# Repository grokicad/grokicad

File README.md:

# GroKi

 AI-powered KiCad understanding for humans. GroKi distills complex schematics into structured data, streams AI explanations, and tracks changes across hardware repos so other engineers, reviewers, and stakeholders (not just EEs) can see what changed, why, and where to look next. Try it out at https://grokicad.com.

## Why
Most people looking at schematics aren’t the original EE, and they need clarity more than another AI authoring tool. Netlists are hard to read, version-control diffing is clunky, and AI tools rarely speak KiCad. GroKi bridges that gap for reviewers, systems engineers, firmware teams, and judges: it parses KiCad projects, summarizes commits and selections with Grok, searches parts, and serves an interactive viewer workflow.

## Key Features
- **Schematic distillation**: Python distiller (`schematic-distiller/`, powered by `kicad-sch-api`) converts `.kicad_sch` into normalized JSON (components, nets, proximities) with cacheable results.
- **Repo + commit intelligence**: Rust backend (`backend/`, Axum + utoipa) initializes repos, lists schematic commits/files, and surfaces commit metadata plus cached distillations.
- **AI assistance (Grok)**:
  - Commit, selection, and repo summaries (`/api/grok/*`)
  - Streaming SSE analysis for selected components with semantic context
  - Obsolete-part replacement suggestions
- **Distill-on-demand API**: `/api/distill` runs or returns cached distillations; `/api/repo/init` primes a repo and reports component/net counts.
- **Part search**: DigiKey keyword/MPN lookup with graceful fallback when not configured.
- **Viewer-friendly data**: Works with `kicanvas/` (TypeScript/WebGL KiCad viewer) and includes ready-made KiCad samples for demos.
- **Example repos**: Use the provided KiCad projects for instant demos:
  - uBMS-2 battery management system: https://github.com/CwbhX/uBMS-2
  - Grok KiCad Watch: https://github.com/CwbhX/GrokKiCADWatch

## Architecture (high level)
- **schematic-distiller/**: Python package + docs; uses `kicad-sch-api` for lossless parsing, connectivity, hierarchy, BOM properties, and MCP tooling.
- **backend/**: Rust Axum service exposing REST + Swagger UI, SSE endpoints, Grok integrations, DigiKey client, and git helpers.
- **database/**: PostgreSQL (Docker) plus Rust `kicad-db` crate for storing distilled JSON, schematic blurbs/overviews, and part metadata.
- **kicanvas/**: Browser-based KiCad viewer (TypeScript/WebGL). Ships with a static debug viewer and docs for embedding.
- **kicad-example-files/**: Curated KiCad projects (includes uBMS-2 and SmartWatch) for quick demonstrations.
- **grokprompts/**: System prompt used by Grok selection summaries.

## Quickstart (judge-friendly)
Prereqs: Docker (for Postgres), Rust toolchain, Python 3.10+, Node (only if you want to rebuild KiCanvas), env var `XAI_API_KEY` for Grok, optional `DIGIKEY_CLIENT_ID/SECRET`.

1) Start the database  
```bash
cd database
chmod +x *.sh
./database-up.sh
```

2) Run the backend (Swagger served at `/swagger-ui`)  
```bash
cd backend
cargo run
# Server on :8080 by default
```

3) Initialize a repo and distill schematics (example: uBMS-2)  
```bash
curl -X POST http://localhost:8080/api/repo/init \
  -H "Content-Type: application/json" \
  -d '{"repo":"CwbhX/uBMS-2"}'
# Response includes component/net counts, schematic file list, and distilled JSON (cached afterward)
```

4) Get commit file list or info  
```bash
curl -X POST http://localhost:8080/api/repo/commit/files \
  -H "Content-Type: application/json" \
  -d '{"repo":"CwbhX/uBMS-2","commit":"<hash>"}'
```

5) Ask Grok for a selection summary (streaming SSE)  
```bash
curl -N -X POST http://localhost:8080/api/grok/selection/stream \
  -H "Content-Type: application/json" \
  -d '{
        "repo":"CwbhX/uBMS-2",
        "commit":"<hash>",
        "component_ids":["U1","R3","C5"],
        "query":"Explain what these parts do together.",
        "thinking_mode":false
      }'
```

6) Try DigiKey search (optional)  
```bash
curl -X POST http://localhost:8080/api/digikey/search \
  -H "Content-Type: application/json" \
  -d '{"query":"ESP32-WROOM"}'
```

7) View data in Swagger UI  
Open `http://localhost:8080/swagger-ui/` to exercise all endpoints.

## Demo scripts & viewer notes
- Use `kicad-example-files/BMS` for uBMS-2 and `kicad-example-files/Smart Watch` for the watch project—both mirror the example repos above.
- `kicanvas/debug/index.html` (or `schematic.html`) can be used to point at distilled outputs or KiCad files if you want an in-browser viewer during judging.

## Developer guide (quick map)
- `backend/src/controllers/…`: Route handlers for repo, distill, grok (AI summaries + SSE), hook (webhooks/refresh), digikey.  
- `backend/src/services/…`: Git helpers, distill runner, DigiKey client.  
- `backend/src/openapi.rs`: Swagger/OpenAPI registration.  
- `database/src`: `kicad-db` crate and scripts to manage Postgres.  
- `schematic-distiller/docs`: Deep docs: getting started, API reference, hierarchy, MCP setup, known limitations.  
- `kicanvas/src`: TypeScript viewer core; `docs/` covers embedding and dev setup.  
- `grokprompts/`: System prompt text used by Grok selection streaming.

## Tips for demos
- **Cache wins**: `/api/repo/init` and `/api/distill` cache distilled JSON in Postgres; repeat calls are instant.  
- **Selections**: Provide explicit `component_ids` to `/api/grok/selection/stream` for tighter answers.  
- **Fallbacks**: If DigiKey creds are missing, the API responds with a clear “not configured” message.  
- **Rate limits**: Grok endpoints call external APIs; if rate-limited, re-run after a short pause.

## Requirements & assumptions
- KiCad 6/7/8 schematics are supported (KiCanvas is v6+; custom fonts in v7 may have gaps).  
- Postgres must be running for caching and part storage.  
- `XAI_API_KEY` required for Grok endpoints; without it, only non-AI paths (distill, repo metadata) will function.  
- Docker scripts reset data when recreating the DB container.

## Known limitations
- Advanced ERC and full global-label connectivity are partial in the underlying parser (see `schematic-distiller/docs/KNOWN_LIMITATIONS.md`).  
- Some Grok endpoints still return placeholder text when external services are unavailable.  
- Viewer: KiCad 5 files are unsupported; best on Chrome/Firefox/Safari desktop.

## Acknowledgments
- Built on `kicad-sch-api`, KiCanvas, Axum, sqlx, and Grok APIs.  
- Example hardware from uBMS-2 and Grok KiCad Watch repos cited above.  
- Created for hackathon judging—fast setup, clear outputs, and transparent architecture.

## Creators
- Clement Hathaway
- Ernest Yeung
- Evan Hekman
- Julian Carrier

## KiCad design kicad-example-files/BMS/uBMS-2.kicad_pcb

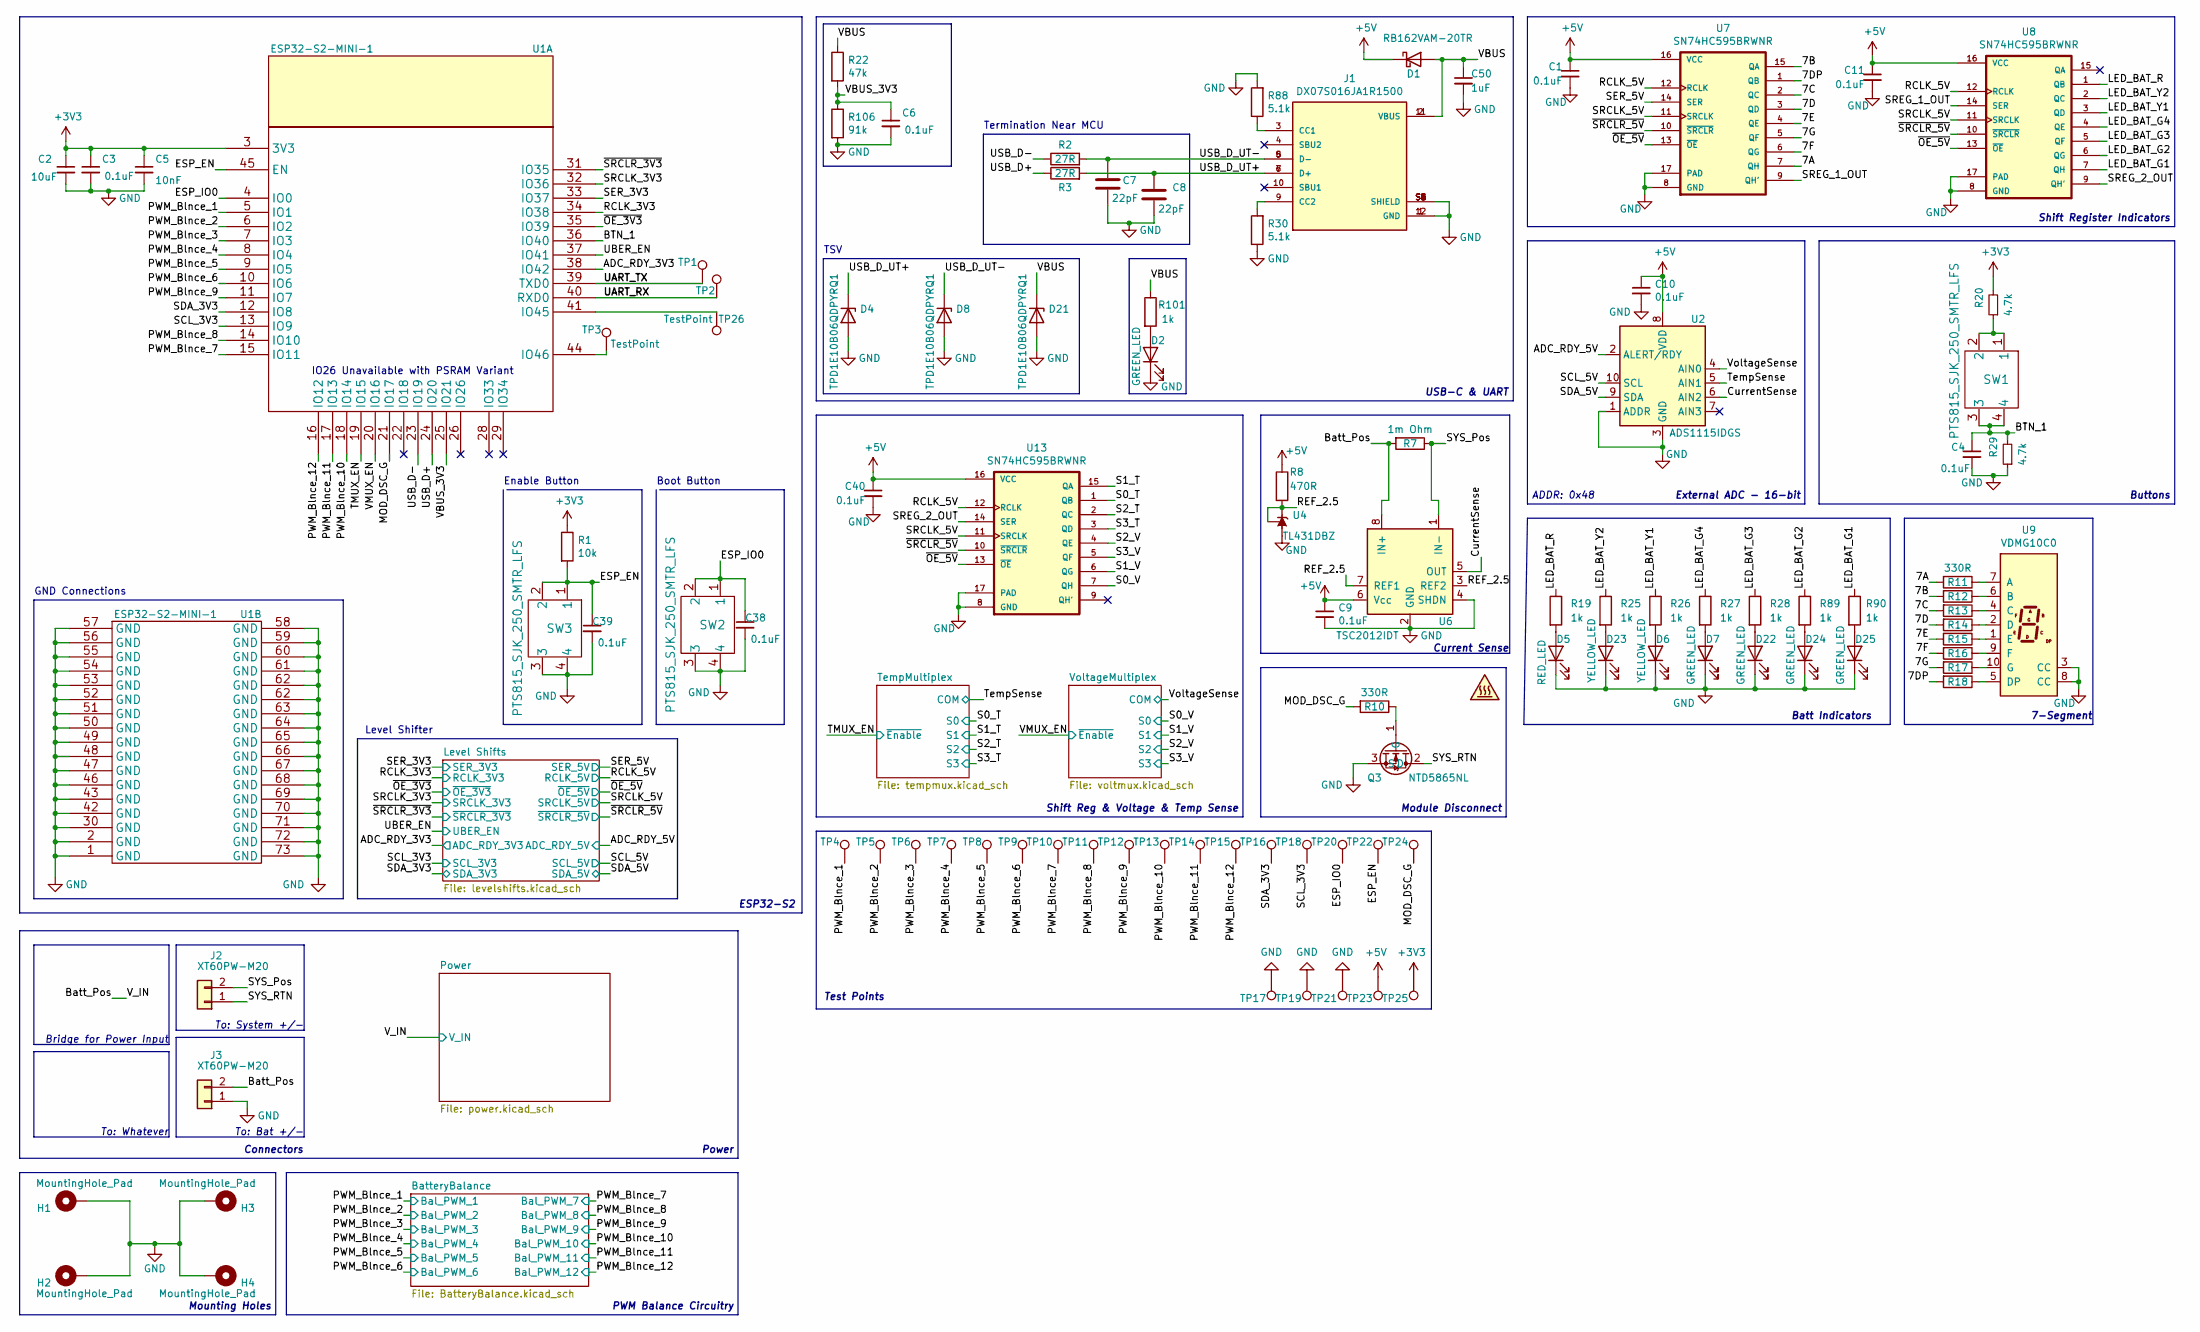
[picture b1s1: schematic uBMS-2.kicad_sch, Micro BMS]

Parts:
C1, C3, C4, C6, C9, C10, C11, C38, C39, C40: 0.1uF; C_0402_1005Metric; Part Number CC0402KRX7R7BB104; Digikey Number 311-1338-1-ND
C2: 10uF; C_0805_2012Metric; Part Number C0805C106K8PACTU; Digikey Number 399-4925-2-ND
C5: 10nF; C_0402_1005Metric; Part Number GCM155R71H103KA55D; Digikey Number 490-4762-1-ND
C7, C8: 22pF; C_0402_1005Metric; Part Number GRM1555C1H220JA01D; Digikey Number 490-5868-1-ND
C50: 1uF; C_0805_2012Metric; Part Number C0805C105Z4VACTU; Digikey Number 399-8011-2-ND
D1: RB162VAM-20TR; D_TUMD2; Part Number RB162VAM-20TR; Digikey Number RB162VAM-20TRTR-ND
D2, D7, D22, D24, D25: GREEN_LED; LED_0603_1608Metric; Part Number 150060VS55040; Digikey Number 732-12017-2-ND
D4, D8, D21: TPD1E10B06QDPYRQ1; D_0402_1005Metric; Part Number TPD1E10B06QDPYRQ1; Digikey Number 296-TPD1E10B06QDPYRQ1TR-ND
D5: RED_LED; LED_0603_1608Metric; Part Number 150060SS55040; Digikey Number 732-12016-2-ND
D6, D23: YELLOW_LED; LED_0603_1608Metric; Part Number 150060YS55040; Digikey Number 732-12018-2-ND
H1, H2, H3, H4: MountingHole_Pad; MountingHole_2.5mm_Pad_TopBottom
J1: DX07S016JA1R1500; PARTREV 1; Digikey Number 670-DX07S016JA1R1500TR-ND
J2, J3: XT60PW-M20
Q3: NTD5865NL; TO-252-2; Part Number NTD5865NLT4G; Digikey Number NTD5865NLT4GOSTR-ND
R1: 10k; R_0402_1005Metric; Part Number RC0402FR-0710KL; Digikey Number 311-10.0KLRCT-ND
R2, R3: 27R; R_0402_1005Metric; Part Number RC0402FR-0727RL; Digikey Number YAG3086CT-ND
R7: 1m Ohm; R_2512_CSNL2512; Part Number CSNL2512FT1L00; Digikey Number CSNL2512FT1L00TR-ND
R8: 470R; R_0402_1005Metric; Part Number RC0402FR-07470RL; Digikey Number 311-470LRCT-ND
R10, R11, R12, R13, R14, R15, R16, R17, R18: 330R; R_0402_1005Metric; Part Number RC0402FR-07330RL; Digikey Number 311-330LRCT-ND
R19, R25, R26, R27, R28, R89, R90, R101: 1k; R_0402_1005Metric; Part Number RC0402FR-071KL; Digikey Number 311-1.00KLRCT-ND
R20, R29: 4.7k; R_0402_1005Metric; Part Number RC0402FR-074K7L; Digikey Number 311-4.7KLRCT-ND
R22: 47k; R_0402_1005Metric; Part Number RC0402FR-0747KL; Digikey Number 311-47.0KLRCT-ND
R30, R88: 5.1k; R_0402_1005Metric; Part Number RC0402FR-075K1L; Digikey Number 311-5.10KLRCT-ND
R106: 91k; R_0402_1005Metric; Part Number RC0402FR-0791KL; Digikey Number 311-91.0KLRCT-ND
SW1, SW2, SW3: PTS815_SJK_250_SMTR_LFS; Part Number PTS815_SJK_250_SMTR_LFS; Digikey Number CKN12216-2-ND
TP1, TP2, TP3, TP4, TP5, TP6, TP7, TP8, TP9, TP10, TP11, TP12, TP13, TP14, TP15, TP16, TP17, TP18, TP19, TP20, TP21, TP22, TP23, TP24, TP25, TP26: TestPoint; TestPoint_Pad_D1.0mm
U1: ESP32-S2-MINI-1
U2: ADS1115IDGS; TSSOP-10_3x3mm_P0.5mm; Part Number ADS1115IDGSR; Digikey Number 296-38849-2-ND
U4: TL431DBZ; SOT-23; Part Number TL431ACDBZR
U6: TSC2012IDT; SO-8_3.9x4.9mm_P1.27mm; Part Number TSC2012IDT; Digikey Number 497-TSC2012IDTTR-ND
U7, U8: SN74HC595BRWNR; QFN40P250X250X50-17N
U9: VDMG10C0; Part Number VDMG10C0; Digikey Number VDMG10C0TR-ND
U13: SN74HC595BRWNR; QFN40P250X250X50-17N; Part Number SN74HC595BRWNR; Digikey Number 296-44070-2-ND

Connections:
+3V3: C2.1, C3.1, C5.1, R1.1, R20.2, TP25.1, U1.3 (3V3); also elsewhere on the board
+5V: C1.1, C9.1, C10.1, C11.1, C40.1, D1.1 (K), R8.1, TP23.1, U2.8 (VDD), U6.6 (Vcc), U7.16 (VCC), U8.16 (VCC), U13.16 (VCC); also elsewhere on the board
/7A: R11.2, U7.7 (QH)
/7B: R12.2, U7.15 (QA)
/7C: R13.2, U7.2 (QC)
/7D: R14.2, U7.3 (QD)
/7DP: R18.2, U7.1 (QB)
/7E: R15.2, U7.4 (QE)
/7F: R16.2, U7.6 (QG)
/7G: R17.2, U7.5 (QF)
/ADC_RDY_3V3: U1.38 (IO42); also elsewhere on the board
/ADC_RDY_5V: U2.2 (ALERT/RDY); also elsewhere on the board
/BTN_1: C4.1, R29.2, SW1.3, SW1.4, U1.36 (IO40)
/Batt_Pos: J3.2, R7.2, U6.8 (IN+); also elsewhere on the board
/CurrentSense: U2.6 (AIN2), U6.5 (OUT)
/ESP_EN: C39.1, R1.2, SW3.1, SW3.2, TP22.1, U1.45 (EN)
/ESP_IO0: C38.1, SW2.1, SW2.2, TP20.1, U1.4 (IO0)
/LED_BAT_G1: R90.1, U8.7 (QH)
/LED_BAT_G2: R89.1, U8.6 (QG)
/LED_BAT_G3: R28.1, U8.5 (QF)
/LED_BAT_G4: R27.1, U8.4 (QE)
/LED_BAT_R: R19.1, U8.1 (QB)
/LED_BAT_Y1: R26.1, U8.3 (QD)
/LED_BAT_Y2: R25.1, U8.2 (QC)
/MOD_DSC_G: R10.2, TP24.1, U1.21 (IO17)
/PWM_Blnce_1: TP4.1, U1.5 (IO1); also elsewhere on the board
/PWM_Blnce_2: TP5.1, U1.6 (IO2); also elsewhere on the board
/PWM_Blnce_3: TP6.1, U1.7 (IO3); also elsewhere on the board
/PWM_Blnce_4: TP7.1, U1.8 (IO4); also elsewhere on the board
/PWM_Blnce_5: TP8.1, U1.9 (IO5); also elsewhere on the board
/PWM_Blnce_6: TP9.1, U1.10 (IO6); also elsewhere on the board
/PWM_Blnce_7: TP10.1, U1.15 (IO11); also elsewhere on the board
/PWM_Blnce_8: TP11.1, U1.14 (IO10); also elsewhere on the board
/PWM_Blnce_9: TP12.1, U1.11 (IO7); also elsewhere on the board
/PWM_Blnce_10: TP13.1, U1.18 (IO14); also elsewhere on the board
/PWM_Blnce_11: TP14.1, U1.17 (IO13); also elsewhere on the board
/PWM_Blnce_12: TP15.1, U1.16 (IO12); also elsewhere on the board
/RCLK_3V3: U1.34 (IO38); also elsewhere on the board
/RCLK_5V: U7.12 (RCLK), U8.12 (RCLK), U13.12 (RCLK); also elsewhere on the board
/REF_2.5: R8.2, U4.1 (K), U4.2 (REF), U6.3 (REF2), U6.7 (REF1)
/S0_T: U13.1 (QB); also elsewhere on the board
/S0_V: U13.7 (QH); also elsewhere on the board
/S1_T: U13.15 (QA); also elsewhere on the board
/S1_V: U13.6 (QG); also elsewhere on the board
/S2_T: U13.2 (QC); also elsewhere on the board
/S2_V: U13.4 (QE); also elsewhere on the board
/S3_T: U13.3 (QD); also elsewhere on the board
/S3_V: U13.5 (QF); also elsewhere on the board
/SCL_3V3: TP18.1, U1.13 (IO9); also elsewhere on the board
/SCL_5V: U2.10 (SCL); also elsewhere on the board
/SDA_3V3: TP16.1, U1.12 (IO8); also elsewhere on the board
/SDA_5V: U2.9 (SDA); also elsewhere on the board
/SER_3V3: U1.33 (IO37); also elsewhere on the board
/SER_5V: U7.14 (SER); also elsewhere on the board
/SRCLK_3V3: U1.32 (IO36); also elsewhere on the board
/SRCLK_5V: U7.11 (SRCLK), U8.11 (SRCLK), U13.11 (SRCLK); also elsewhere on the board
/SREG_1_OUT: U7.9 (QH'), U8.14 (SER)
/SREG_2_OUT: U8.9 (QH'), U13.14 (SER)
/SYS_Pos: J2.2, R7.1, U6.1 (IN-)
/SYS_RTN: J2.1, Q3.2 (D)
/TMUX_EN: U1.19 (IO15); also elsewhere on the board
/TempSense: U2.5 (AIN1); also elsewhere on the board
/UART_RX: TP2.1, U1.40 (RXD0)
/UART_TX: TP1.1, U1.39 (TXD0)
/UBER_EN: U1.37 (IO41); also elsewhere on the board
/USB_D+: R3.1, U1.24 (IO20)
/USB_D-: R2.1, U1.23 (IO19)
/USB_D_UT+: C8.1, D4.1 (K), J1.6 (D+), J1.7 (D+), R3.2
/USB_D_UT-: C7.1, D8.1 (K), J1.5 (D-), J1.8 (D-), R2.2
/VBUS: C50.1, D1.2 (A), D21.1 (K), J1.2 (VBUS), J1.11 (VBUS), R22.1, R101.1
/VBUS_3V3: C6.1, R22.2, R106.1, U1.25 (IO21)
/VMUX_EN: U1.20 (IO16); also elsewhere on the board
/VoltageSense: U2.4 (AIN0); also elsewhere on the board
/~OE_3V3: U1.35 (IO39); also elsewhere on the board
/~OE_5V: U7.13 (~OE), U8.13 (~OE), U13.13 (~OE); also elsewhere on the board
/~SRCLR_3V3: U1.31 (IO35); also elsewhere on the board
/~SRCLR_5V: U7.10 (~SRCLR), U8.10 (~SRCLR), U13.10 (~SRCLR); also elsewhere on the board
GND: C1.2, C2.2, C3.2, C4.2, C5.2, C6.2, C7.2, C8.2, C9.2, C10.2, C11.2, C38.2, C39.2, C40.2, C50.2, D2.1 (K), D4.2 (A), D5.1 (K), D6.1 (K), D7.1 (K), D8.2 (A), D21.2 (A), D22.1 (K), D23.1 (K), D24.1 (K), D25.1 (K), H1.1, H2.1, H3.1, H4.1, J1.1 (GND), J1.12 (GND), J1.S1 (SHIELD), J1.S2 (SHIELD), J1.S3 (SHIELD), J1.S4 (SHIELD), J1.S5 (SHIELD), J1.S6 (SHIELD), J3.1, Q3.3 (S), R29.1, R30.1, R88.2, R106.2, SW2.3, SW2.4, SW3.3, SW3.4, TP17.1, TP19.1, TP21.1, U1.1 (GND), U1.2 (GND), U1.30 (GND), U1.42 (GND), U1.43 (GND), U1.46 (GND), U1.47 (GND), U1.48 (GND), U1.49 (GND), U1.50 (GND), U1.51 (GND), U1.52 (GND), U1.53 (GND), U1.54 (GND), U1.55 (GND), U1.56 (GND), U1.57 (GND), U1.58 (GND), U1.59 (GND), U1.60 (GND), U1.61 (GND), U1.62 (GND), U1.63 (GND), U1.64 (GND), U1.65 (GND), U1.66 (GND), U1.67 (GND), U1.68 (GND), U1.69 (GND), U1.70 (GND), U1.71 (GND), U1.72 (GND), U1.73 (GND), U2.1 (ADDR), U2.3 (GND), U4.3 (A), U6.2 (GND), U6.4 (SHDN), U7.8 (GND), U7.17 (PAD), U8.8 (GND), U8.17 (PAD), U9.3 (CC), U9.8 (CC), U13.8 (GND), U13.17 (PAD); also elsewhere on the board
unnamed: D2.2 (A), R101.2
unnamed: D5.2 (A), R19.2
unnamed: D6.2 (A), R26.2
unnamed: D7.2 (A), R27.2
unnamed: D22.2 (A), R28.2
unnamed: D23.2 (A), R25.2
unnamed: D24.2 (A), R89.2
unnamed: D25.2 (A), R90.2
unnamed: J1.3 (CC1), R88.1
unnamed: J1.9 (CC2), R30.2
unnamed: Q3.1 (G), R10.1
unnamed: R11.1, U9.7 (A)
unnamed: R12.1, U9.6 (B)
unnamed: R13.1, U9.4 (C)
unnamed: R14.1, U9.2 (D)
unnamed: R15.1, U9.1 (E)
unnamed: R16.1, U9.9 (F)
unnamed: R17.1, U9.10 (G)
unnamed: R18.1, U9.5 (DP)
unnamed: R20.1, SW1.1, SW1.2
unnamed: TP3.1, U1.44 (IO46)
unnamed: TP26.1, U1.41 (IO45)

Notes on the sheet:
IO26 Unavailable with PSRAM Variant
To: System +/-
ESP32-S2
Shift Reg & Voltage & Temp Sense
Mounting Holes
Level Shifter
Test Points
Module Disconnect
Shift Register Indicators
To: Whatever
GND Connections
Buttons
Enable Button
Connectors
Batt Indicators
Boot Button
To: Bat +/-
PWM Balance Circuitry
ADDR: 0x48
USB-C & UART
7-Segment
Power
Termination Near MCU
External ADC - 16-bit
Bridge for Power Input
TSV
Current Sense

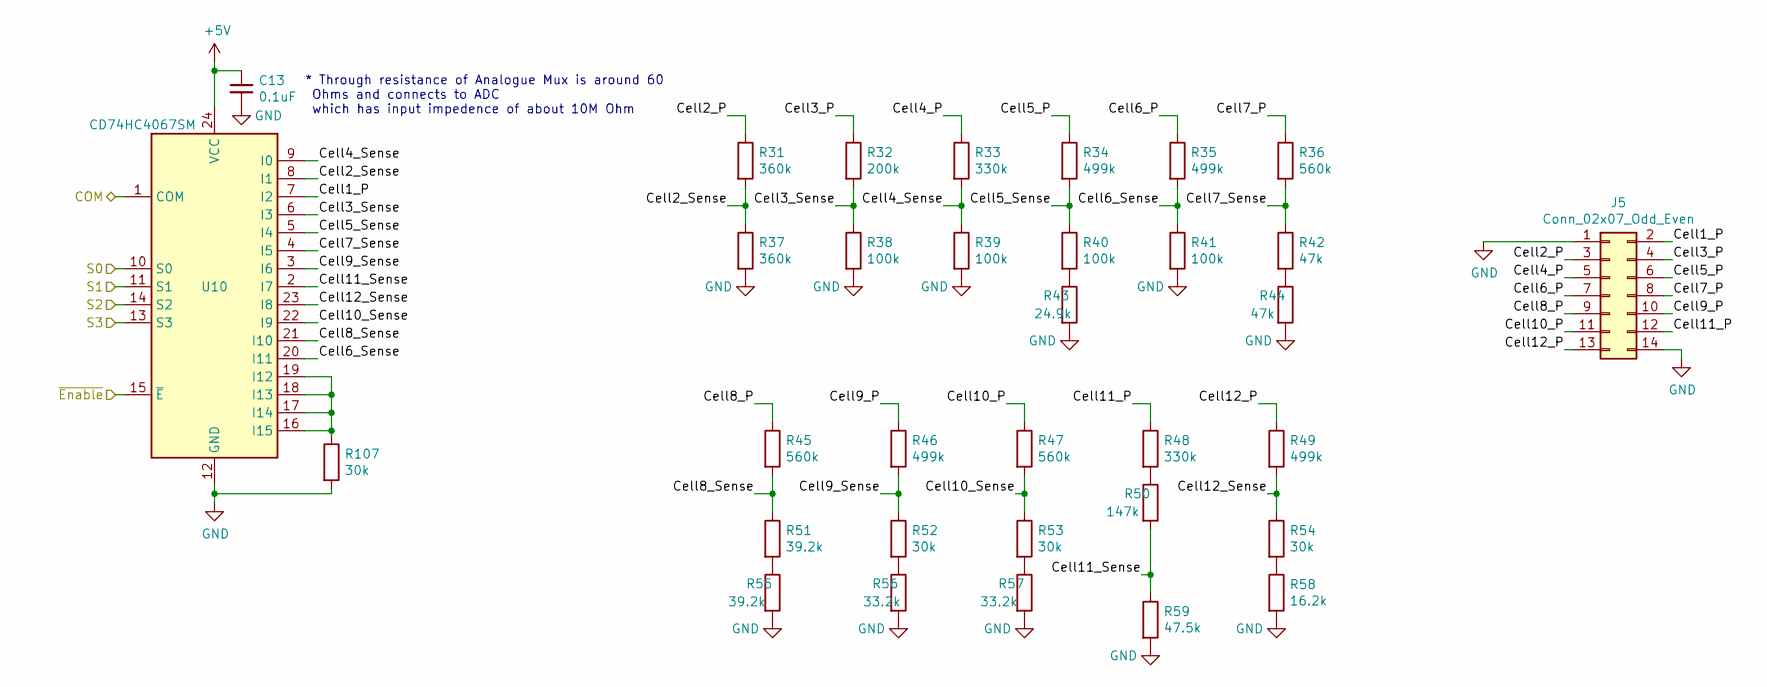
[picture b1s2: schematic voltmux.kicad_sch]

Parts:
C13: 0.1uF; C_0402_1005Metric; Part Number CC0402KRX7R7BB104; Digikey Number 311-1338-1-ND
J5: Conn_02x07_Odd_Even; Molex_Milli_Grid_0878325623_TopBottom; Part Number 0878325623; Digikey Number WM6815TR-ND
R31, R37: 360k; R_0402_1005Metric; Part Number RC0402FR-07360KL; Digikey Number 311-360KLRCT-ND
R32: 200k; R_0402_1005Metric; Part Number RC0402FR-07200KL; Digikey Number 311-200KLRCT-ND
R33, R48: 330k; R_0402_1005Metric; Part Number RC0402JR-07330KL; Digikey Number 311-330KJRCT-ND
R34, R35, R46, R49: 499k; R_0402_1005Metric; Part Number RC0402FR-07499KL; Digikey Number 311-499KLRCT-ND
R36, R45, R47: 560k; R_0402_1005Metric; Part Number RC0402FR-07560KL; Digikey Number 311-560KLRCT-ND
R38, R39, R40, R41: 100k; R_0402_1005Metric; Part Number RC0402FR-07100KL; Digikey Number 311-100KLRCT-ND
R42, R44: 47k; R_0402_1005Metric; Part Number RC0402FR-0747KL; Digikey Number 311-47.0KLRCT-ND
R43: 24.9k; R_0402_1005Metric; Part Number RC0402FR-0724K9L; Digikey Number 311-24.9KLRCT-ND
R50: 147k; R_0402_1005Metric; Part Number RC0402FR-07147KL; Digikey Number YAG2981CT-ND
R51, R55: 39.2k; R_0402_1005Metric; Part Number RC0402FR-0739K2L; Digikey Number 311-39.2KLRCT-ND
R52, R53, R54, R107: 30k; R_0402_1005Metric; Part Number RC0402FR-0730KL; Digikey Number 311-30.0KLRCT-ND
R56, R57: 33.2k; R_0402_1005Metric; Part Number RC0402FR-0733K2L; Digikey Number 311-33.2KLRCT-ND
R58: 16.2k; R_0402_1005Metric; Part Number RC0402FR-0716K2L; Digikey Number 311-16.2KLRCT-ND
R59: 47.5k; R_0402_1005Metric; Part Number RC0402FR-0747K5L; Digikey Number 311-47.5KLRCT-ND
U10: CD74HC4067SM; SSOP-24_5.3x8.2mm_P0.65mm; Part Number CD74HC4067SM96; Digikey Number 296-9226-2-ND

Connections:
+5V: C13.1, U10.24 (VCC); also elsewhere on the board
/S0_V: U10.10 (S0); also elsewhere on the board
/S1_V: U10.11 (S1); also elsewhere on the board
/S2_V: U10.14 (S2); also elsewhere on the board
/S3_V: U10.13 (S3); also elsewhere on the board
/VMUX_EN: U10.15 (~E); also elsewhere on the board
/VoltageMultiplex/Cell1_P: J5.2, U10.7 (I2)
/VoltageMultiplex/Cell2_P: J5.3, R31.1
/VoltageMultiplex/Cell2_Sense: R31.2, R37.1, U10.8 (I1)
/VoltageMultiplex/Cell3_P: J5.4, R32.1
/VoltageMultiplex/Cell3_Sense: R32.2, R38.1, U10.6 (I3)
/VoltageMultiplex/Cell4_P: J5.5, R33.1
/VoltageMultiplex/Cell4_Sense: R33.2, R39.1, U10.9 (I0)
/VoltageMultiplex/Cell5_P: J5.6, R34.1
/VoltageMultiplex/Cell5_Sense: R34.2, R40.1, U10.5 (I4)
/VoltageMultiplex/Cell6_P: J5.7, R35.1
/VoltageMultiplex/Cell6_Sense: R35.2, R41.1, U10.20 (I11)
/VoltageMultiplex/Cell7_P: J5.8, R36.1
/VoltageMultiplex/Cell7_Sense: R36.2, R42.1, U10.4 (I5)
/VoltageMultiplex/Cell8_P: J5.9, R45.1
/VoltageMultiplex/Cell8_Sense: R45.2, R51.1, U10.21 (I10)
/VoltageMultiplex/Cell9_P: J5.10, R46.1
/VoltageMultiplex/Cell9_Sense: R46.2, R52.1, U10.3 (I6)
/VoltageMultiplex/Cell10_P: J5.11, R47.1
/VoltageMultiplex/Cell10_Sense: R47.2, R53.1, U10.22 (I9)
/VoltageMultiplex/Cell11_P: J5.12, R48.1
/VoltageMultiplex/Cell11_Sense: R50.2, R59.1, U10.2 (I7)
/VoltageMultiplex/Cell12_P: J5.13, R49.1
/VoltageMultiplex/Cell12_Sense: R49.2, R54.1, U10.23 (I8)
/VoltageSense: U10.1 (COM); also elsewhere on the board
GND: C13.2, J5.1, J5.14, R37.2, R38.2, R39.2, R41.2, R43.2, R44.2, R55.2, R56.2, R57.2, R58.2, R59.2, R107.2, U10.12 (GND); also elsewhere on the board
unnamed: R40.2, R43.1
unnamed: R42.2, R44.1
unnamed: R48.2, R50.1
unnamed: R51.2, R55.1
unnamed: R52.2, R56.1
unnamed: R53.2, R57.1
unnamed: R54.2, R58.1
unnamed: R107.1, U10.16 (I15), U10.17 (I14), U10.18 (I13), U10.19 (I12)

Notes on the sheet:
* Through resistance of Analogue Mux is around 60 Ohms and connects to ADC which has input impedence of about 10M Ohm

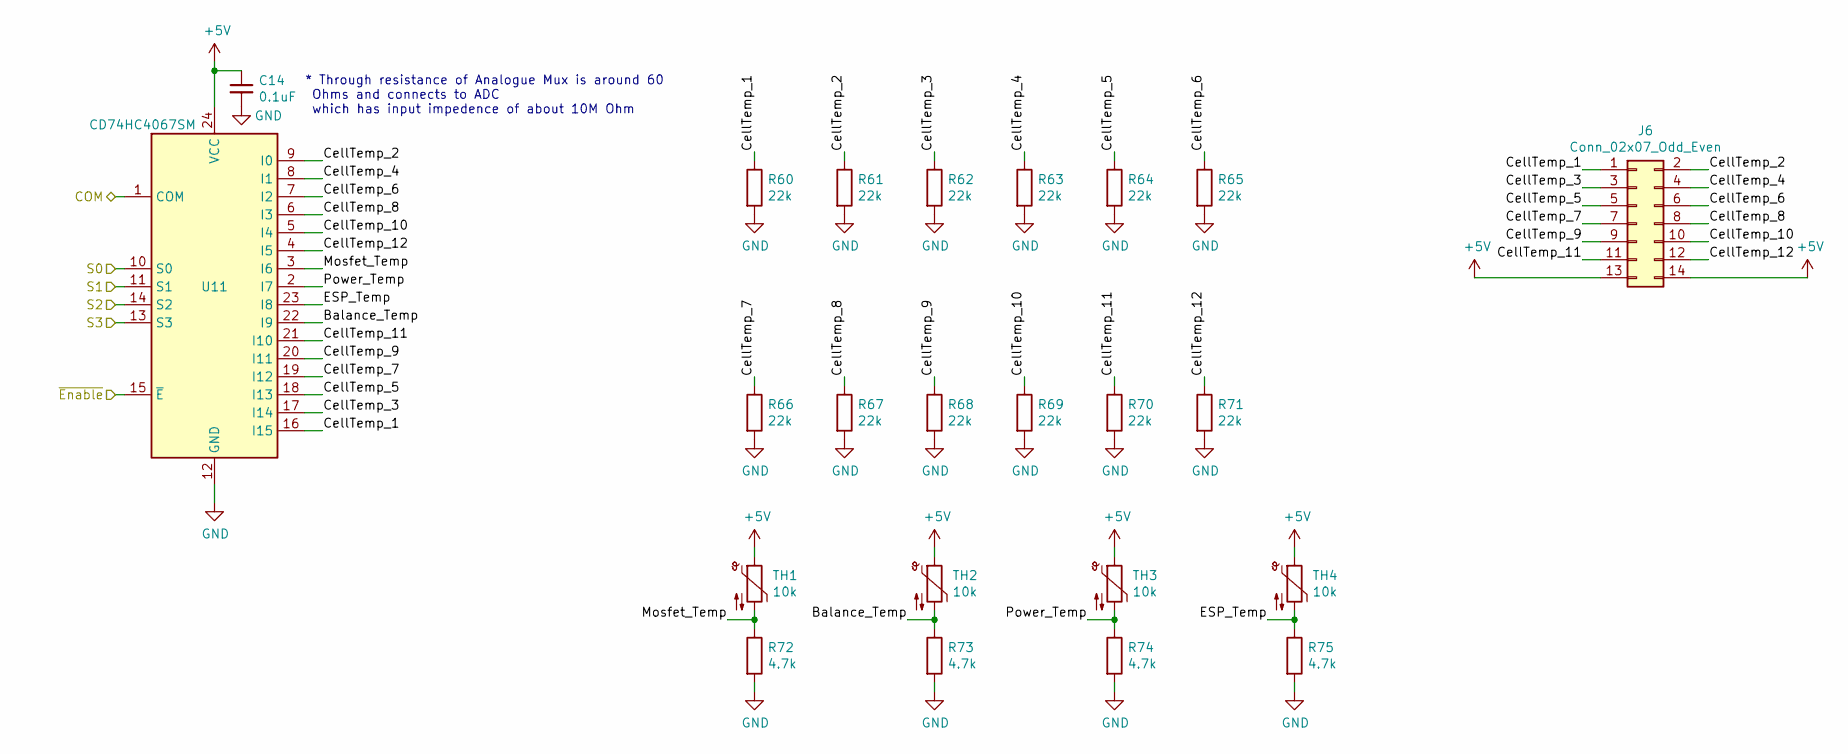
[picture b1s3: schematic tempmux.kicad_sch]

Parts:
C14: 0.1uF; C_0402_1005Metric; Part Number CC0402KRX7R7BB104; Digikey Number 311-1338-1-ND
J6: Conn_02x07_Odd_Even; Molex_Milli_Grid_0878325623_TopBottom; Part Number 0878325623; Digikey Number WM6815TR-ND
R60, R61, R62, R63, R64, R65, R66, R67, R68, R69, R70, R71: 22k; R_0402_1005Metric; Part Number RC0402FR-0722KL; Digikey Number 311-22.0KLRCT-ND
R72, R73, R74, R75: 4.7k; R_0402_1005Metric; Part Number RC0402FR-074K7L; Digikey Number 311-4.7KLRCT-ND
TH1, TH2, TH3, TH4: 10k; R_0402_1005Metric; Part Number NTCG103JF103FT1; Digikey Number 445-2550-1-ND
U11: CD74HC4067SM; SSOP-24_5.3x8.2mm_P0.65mm; Part Number CD74HC4067SM96; Digikey Number 296-9226-2-ND

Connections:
+5V: C14.1, J6.13, J6.14, TH1.1, TH2.1, TH3.1, TH4.1, U11.24 (VCC); also elsewhere on the board
/S0_T: U11.10 (S0); also elsewhere on the board
/S1_T: U11.11 (S1); also elsewhere on the board
/S2_T: U11.14 (S2); also elsewhere on the board
/S3_T: U11.13 (S3); also elsewhere on the board
/TMUX_EN: U11.15 (~E); also elsewhere on the board
/TempMultiplex/Balance_Temp: R73.1, TH2.2, U11.22 (I9)
/TempMultiplex/CellTemp_1: J6.1, R60.1, U11.16 (I15)
/TempMultiplex/CellTemp_2: J6.2, R61.1, U11.9 (I0)
/TempMultiplex/CellTemp_3: J6.3, R62.1, U11.17 (I14)
/TempMultiplex/CellTemp_4: J6.4, R63.1, U11.8 (I1)
/TempMultiplex/CellTemp_5: J6.5, R64.1, U11.18 (I13)
/TempMultiplex/CellTemp_6: J6.6, R65.1, U11.7 (I2)
/TempMultiplex/CellTemp_7: J6.7, R66.1, U11.19 (I12)
/TempMultiplex/CellTemp_8: J6.8, R67.1, U11.6 (I3)
/TempMultiplex/CellTemp_9: J6.9, R68.1, U11.20 (I11)
/TempMultiplex/CellTemp_10: J6.10, R69.1, U11.5 (I4)
/TempMultiplex/CellTemp_11: J6.11, R70.1, U11.21 (I10)
/TempMultiplex/CellTemp_12: J6.12, R71.1, U11.4 (I5)
/TempMultiplex/ESP_Temp: R75.1, TH4.2, U11.23 (I8)
/TempMultiplex/Mosfet_Temp: R72.1, TH1.2, U11.3 (I6)
/TempMultiplex/Power_Temp: R74.1, TH3.2, U11.2 (I7)
/TempSense: U11.1 (COM); also elsewhere on the board
GND: C14.2, R60.2, R61.2, R62.2, R63.2, R64.2, R65.2, R66.2, R67.2, R68.2, R69.2, R70.2, R71.2, R72.2, R73.2, R74.2, R75.2, U11.12 (GND); also elsewhere on the board

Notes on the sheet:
* Through resistance of Analogue Mux is around 60 Ohms and connects to ADC which has input impedence of about 10M Ohm

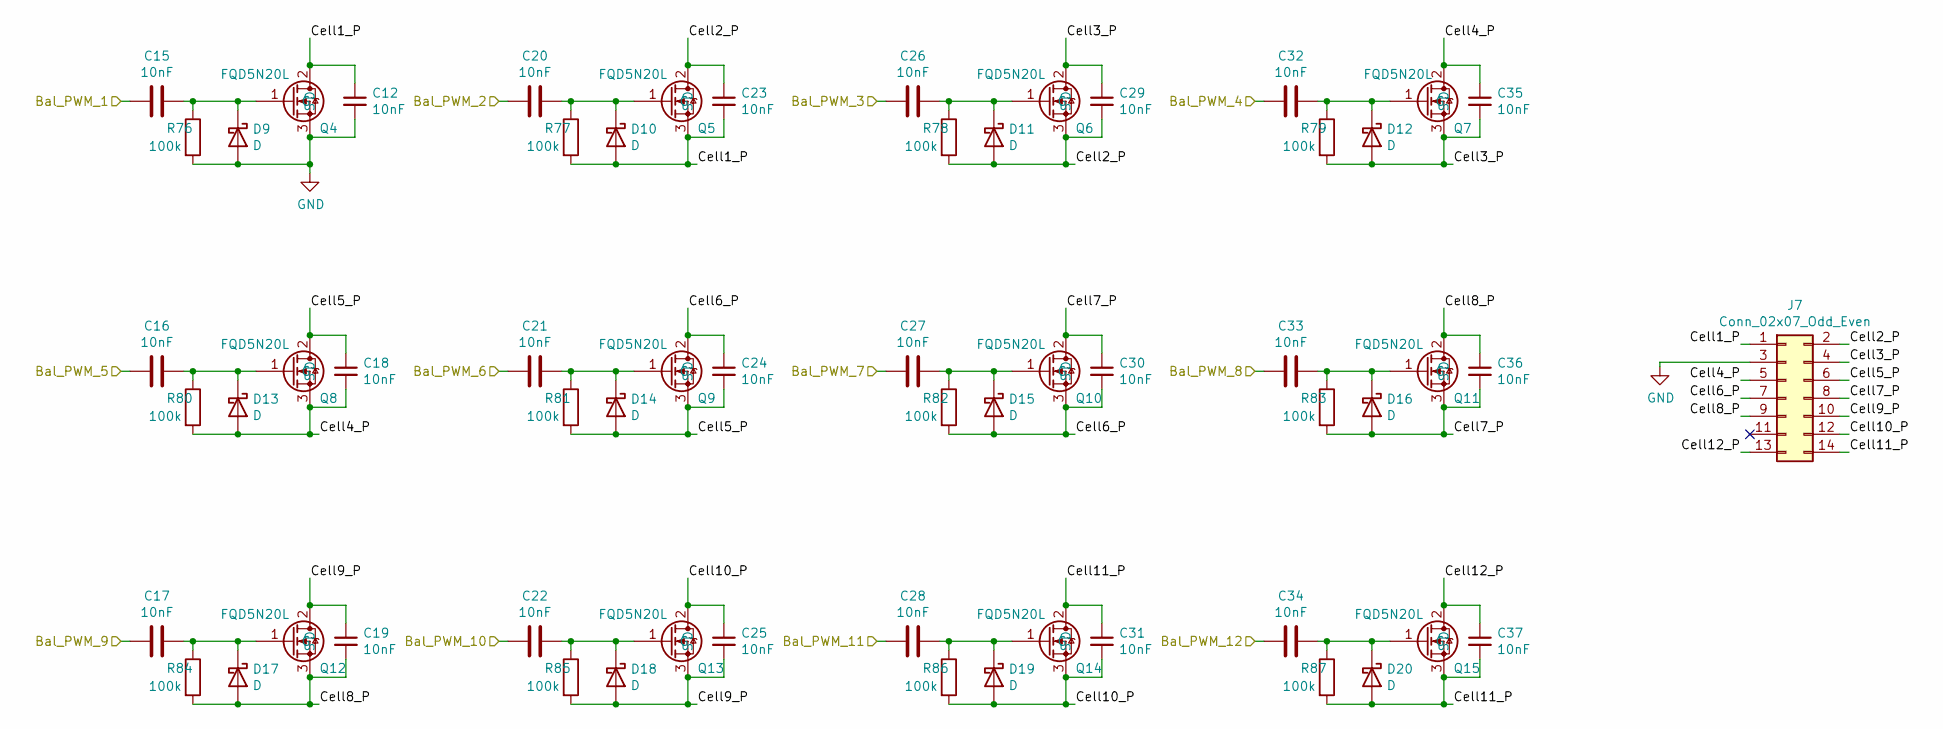
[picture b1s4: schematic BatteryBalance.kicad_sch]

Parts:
C12, C15, C16, C17, C18, C19, C20, C21, C22, C23, C24, C25, C26, C27, C28, C29, C30, C31, C32, C33, C34, C35, C36, C37: 10nF; C_0402_1005Metric; Part Number GCM155R71H103KA55D; Digikey Number 490-4762-1-ND
D9, D10, D11, D12, D13, D14, D15, D16, D17, D18, D19, D20: D; D_1206_3216Metric; Part Number SD1206S020S1R0; Digikey Number 478-7803-1-ND
J7: Conn_02x07_Odd_Even; Molex_Milli_Grid_0878325623_TopBottom; Part Number 0878325623; Digikey Number WM6815TR-ND
Q4, Q5, Q6, Q7, Q8, Q9, Q10, Q11, Q12, Q13, Q14, Q15: FQD5N20L; TO-252-2; Part Number FQD5N20LTM; Digikey Number FQD5N20LTMTR-ND
R76, R77, R78, R79, R80, R81, R82, R83, R84, R85, R86, R87: 100k; R_1206_3216Metric; Part Number RC1206FR-13100KL; Digikey Number 13-RC1206FR-13100KLCT-ND

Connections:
/BatteryBalance/Cell1_P: C12.1, C23.2, D10.2 (A), J7.1, Q4.2 (D), Q5.3 (S), R77.2
/BatteryBalance/Cell2_P: C23.1, C29.2, D11.2 (A), J7.2, Q5.2 (D), Q6.3 (S), R78.2
/BatteryBalance/Cell3_P: C29.1, C35.2, D12.2 (A), J7.4, Q6.2 (D), Q7.3 (S), R79.2
/BatteryBalance/Cell4_P: C18.2, C35.1, D13.2 (A), J7.5, Q7.2 (D), Q8.3 (S), R80.2
/BatteryBalance/Cell5_P: C18.1, C24.2, D14.2 (A), J7.6, Q8.2 (D), Q9.3 (S), R81.2
/BatteryBalance/Cell6_P: C24.1, C30.2, D15.2 (A), J7.7, Q9.2 (D), Q10.3 (S), R82.2
/BatteryBalance/Cell7_P: C30.1, C36.2, D16.2 (A), J7.8, Q10.2 (D), Q11.3 (S), R83.2
/BatteryBalance/Cell8_P: C19.2, C36.1, D17.2 (A), J7.9, Q11.2 (D), Q12.3 (S), R84.2
/BatteryBalance/Cell9_P: C19.1, C25.2, D18.2 (A), J7.10, Q12.2 (D), Q13.3 (S), R85.2
/BatteryBalance/Cell10_P: C25.1, C31.2, D19.2 (A), J7.12, Q13.2 (D), Q14.3 (S), R86.2
/BatteryBalance/Cell11_P: C31.1, C37.2, D20.2 (A), J7.14, Q14.2 (D), Q15.3 (S), R87.2
/BatteryBalance/Cell12_P: C37.1, J7.13, Q15.2 (D)
/PWM_Blnce_1: C15.2; also elsewhere on the board
/PWM_Blnce_2: C20.2; also elsewhere on the board
/PWM_Blnce_3: C26.2; also elsewhere on the board
/PWM_Blnce_4: C32.2; also elsewhere on the board
/PWM_Blnce_5: C16.2; also elsewhere on the board
/PWM_Blnce_6: C21.2; also elsewhere on the board
/PWM_Blnce_7: C27.2; also elsewhere on the board
/PWM_Blnce_8: C33.2; also elsewhere on the board
/PWM_Blnce_9: C17.2; also elsewhere on the board
/PWM_Blnce_10: C22.2; also elsewhere on the board
/PWM_Blnce_11: C28.2; also elsewhere on the board
/PWM_Blnce_12: C34.2; also elsewhere on the board
GND: C12.2, D9.2 (A), J7.3, Q4.3 (S), R76.2; also elsewhere on the board
unnamed: C15.1, D9.1 (K), Q4.1 (G), R76.1
unnamed: C16.1, D13.1 (K), Q8.1 (G), R80.1
unnamed: C17.1, D17.1 (K), Q12.1 (G), R84.1
unnamed: C20.1, D10.1 (K), Q5.1 (G), R77.1
unnamed: C21.1, D14.1 (K), Q9.1 (G), R81.1
unnamed: C22.1, D18.1 (K), Q13.1 (G), R85.1
unnamed: C26.1, D11.1 (K), Q6.1 (G), R78.1
unnamed: C27.1, D15.1 (K), Q10.1 (G), R82.1
unnamed: C28.1, D19.1 (K), Q14.1 (G), R86.1
unnamed: C32.1, D12.1 (K), Q7.1 (G), R79.1
unnamed: C33.1, D16.1 (K), Q11.1 (G), R83.1
unnamed: C34.1, D20.1 (K), Q15.1 (G), R87.1

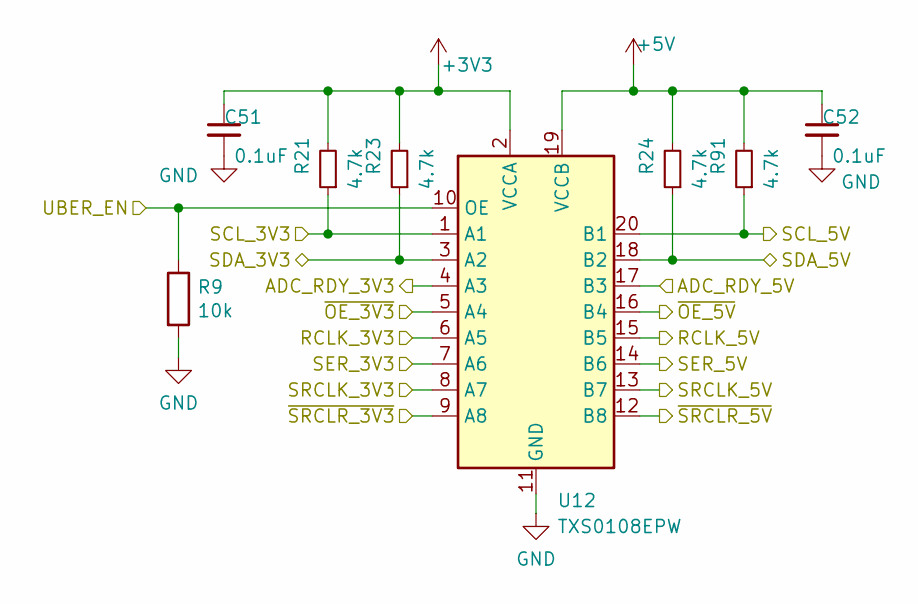
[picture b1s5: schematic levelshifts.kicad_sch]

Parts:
C51, C52: 0.1uF; C_0402_1005Metric; Part Number CC0402KRX7R7BB104; Digikey Number 311-1338-1-ND
R9: 10k; R_0402_1005Metric; Part Number RC0402FR-0710KL; Digikey Number 311-10.0KLRCT-ND
R21, R23, R24, R91: 4.7k; R_0402_1005Metric; Part Number RC0402FR-074K7L; Digikey Number 311-4.7KLRCT-ND
U12: TXS0108EPW; TSSOP-20_4.4x6.5mm_P0.65mm

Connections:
+3V3: C51.1, R21.2, R23.2, U12.2 (VCCA); also elsewhere on the board
+5V: C52.1, R24.2, R91.2, U12.19 (VCCB); also elsewhere on the board
/ADC_RDY_3V3: U12.4 (A3); also elsewhere on the board
/ADC_RDY_5V: U12.17 (B3); also elsewhere on the board
/RCLK_3V3: U12.6 (A5); also elsewhere on the board
/RCLK_5V: U12.15 (B5); also elsewhere on the board
/SCL_3V3: R21.1, U12.1 (A1); also elsewhere on the board
/SCL_5V: R91.1, U12.20 (B1); also elsewhere on the board
/SDA_3V3: R23.1, U12.3 (A2); also elsewhere on the board
/SDA_5V: R24.1, U12.18 (B2); also elsewhere on the board
/SER_3V3: U12.7 (A6); also elsewhere on the board
/SER_5V: U12.14 (B6); also elsewhere on the board
/SRCLK_3V3: U12.8 (A7); also elsewhere on the board
/SRCLK_5V: U12.13 (B7); also elsewhere on the board
/UBER_EN: R9.1, U12.10 (OE); also elsewhere on the board
/~OE_3V3: U12.5 (A4); also elsewhere on the board
/~OE_5V: U12.16 (B4); also elsewhere on the board
/~SRCLR_3V3: U12.9 (A8); also elsewhere on the board
/~SRCLR_5V: U12.12 (B8); also elsewhere on the board
GND: C51.2, C52.2, R9.2, U12.11 (GND); also elsewhere on the board

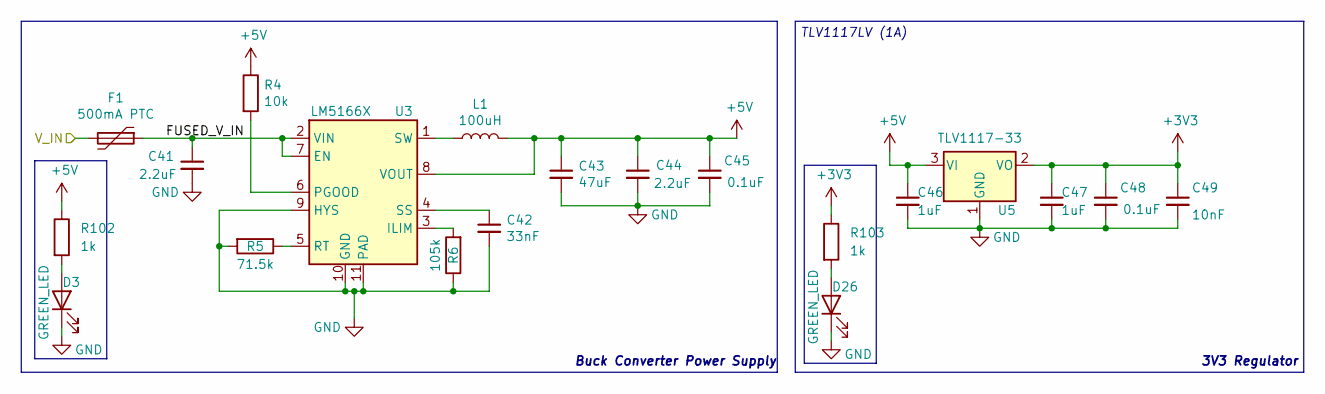
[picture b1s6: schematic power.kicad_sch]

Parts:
C41: 2.2uF; C_1206_3216Metric; Part Number HMK316AC7225KL-TE; Digikey Number 587-5026-2-ND
C42: 33nF; C_0402_1005Metric; Part Number CC0402KRX7R9BB332; Digikey Number 311-1034-1-ND
C43: 47uF; C_1206_3216Metric; Part Number JMK316ABJ476MLHT; Digikey Number 587-3399-2-ND
C44: 2.2uF; C_0402_1005Metric; Part Number GRM155C81C225ME15D; Digikey Number 490-10444-1-ND
C45, C48: 0.1uF; C_0402_1005Metric; Part Number CC0402KRX7R7BB104; Digikey Number 311-1338-1-ND
C46, C47: 1uF; C_0805_2012Metric; Part Number C0805C105Z4VACTU; Digikey Number 399-8011-2-ND
C49: 10nF; C_0402_1005Metric; Part Number GCM155R71H103KA55D; Digikey Number 490-4762-1-ND
D3, D26: GREEN_LED; LED_0603_1608Metric; Part Number 150060VS55040; Digikey Number 732-12017-2-ND
F1: 500mA PTC; 0ZCJ0050FF2G_3216X125N; Part Number 0ZCJ0050FF2G; Digikey Number 507-1802-2-ND
L1: 100uH; 1267AY-101M=P3; Part Number 1267AY-101M=P3; Digikey Number 490-10826-2-ND
R4: 10k; R_0402_1005Metric; Part Number RC0402FR-0710KL; Digikey Number 311-10.0KLRCT-ND
R5: 71.5k; R_0402_1005Metric; Part Number RC0402FR-0771K5L; Digikey Number YAG3222CT-ND
R6: 105k; R_0402_1005Metric; Part Number RC0402FR-07105KL; Digikey Number YAG2946CT-ND
R102, R103: 1k; R_0402_1005Metric; Part Number RC0402FR-071KL; Digikey Number 311-1.00KLRCT-ND
U3: LM5166X; Texas_S-PVSON-N10_ThermalVias; Part Number LM5166XDRCR; Digikey Number 296-47662-2-ND
U5: TLV1117-33; SOT-223-3_TabPin2; Part Number TLV1117LV33DCYR; Digikey Number 296-28778-2-ND

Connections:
+3V3: C47.1, C48.1, C49.1, R103.1, U5.2 (VO); also elsewhere on the board
+5V: C43.1, C44.1, C45.1, C46.1, L1.2, R4.1, R102.1, U3.8 (VOUT), U5.3 (VI); also elsewhere on the board
/Batt_Pos: F1.2; also elsewhere on the board
/Power/FUSED_V_IN: C41.1, F1.1, U3.2 (VIN), U3.7 (EN)
GND: C41.2, C42.2, C43.2, C44.2, C45.2, C46.2, C47.2, C48.2, C49.2, D3.1 (K), D26.1 (K), R5.2, R6.1, U3.9 (HYS), U3.10 (GND), U3.11 (PAD), U5.1 (GND); also elsewhere on the board
unnamed: C42.1, U3.4 (SS)
unnamed: D3.2 (A), R102.2
unnamed: D26.2 (A), R103.2
unnamed: L1.1, U3.1 (SW)
unnamed: R4.2, U3.6 (PGOOD)
unnamed: R5.1, U3.5 (RT)
unnamed: R6.2, U3.3 (ILIM)

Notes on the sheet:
Buck Converter Power Supply
3V3 Regulator
TLV1117LV (1A)

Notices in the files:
parts and their libraries:
Copyright 2016 Accelerated Designs. All rights reserved.
